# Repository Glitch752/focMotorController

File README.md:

# FOCMotorController

A 12v brushless DC motor controller capable of [field-oriented control](https://en.wikipedia.org/wiki/Vector_control_(motor)) (also known as vector control), which is a control system concept that can improve the efficiency and power output of motors using current-based feedback.

I wanted to learn how field-oriented control systems (and brushless motor controllers in general) work, so I made a PCB from scratch!

</img>

## Design goals
- Allow 30-amp continuous operation
- Run field-oriented control
- Runs off an RP2040 Arduino devboard
- Operate at relatively high efficiency: I don't have a specific goal in mind, but ideally it would experience less than a few watts loss at peak load
- Allow controlling the [REV NEO](https://www.revrobotics.com/rev-21-1650/) series motors from the FRC ecosystem because I have access to many old ones.
- Record accurate quadrature encoder readings for tight closed-loop control
- Build for under $200

## Bill of materials

There are a few main components I needed to choose for this project:
- **MOSFETs:** This is pretty much just a tradeoff between efficiency, size, and price. I landed on the STM [STP55NF06L](https://www.st.com/content/ccc/resource/technical/document/datasheet/49/c5/a8/71/93/60/4f/86/CD00002690.pdf/files/CD00002690.pdf/jcr:content/translations/en.CD00002690.pdf) power MOSFET,
which has a very low static resistance when on with a gate voltage of >10V. At only 3.3V, the resistance is quite high, meaning we need a gate driver circuit to improve the driver's efficiency.
- **Gate drivers**: I chose the [IR2104](https://www.infineon.com/dgdl/Infineon-IR2104-DS-v01_00-EN.pdf?fileId=5546d462533600a4015355c7c1c31671) half-bridge gate drivers primarily because they're cheap and widely available.
Also, since they're half-bridge, they manage both the voltage and ground MOSFETs for their phase, which simplifies the control logic.
- **Current measurement circuitry**: There are [quite a few methods available for sensing current](https://www.nxp.com/docs/en/application-note/AN14164.pdf) in motor controllers, but the simplest is using a shunt resistor and relying on Ohm's law.
This is what I ended up doing. I use a [INA240 amplifier](https://www.ti.com/lit/ds/symlink/ina240.pdf) reading across a 6mΩ resistor to convert the tiny voltage potential difference to something readable by the microcontroller.
I'm interested to see what the signal-to-noise ratio will look like.
- Other miscellaneous things like logic level shifters because we're using a 3.3v microcontroller and 5v encoders. All components use a relatively large form-factor where possible to make hand-soldering simpler (altough there are a few tiny SMT components).

Here are all the components required and their price as of July 2025 from JLCPCB.
Of course, many of these can be sourced cheaper elsewhere and soldered manually.

|Name     |Purpose|Quantity|JLC part number|Total Price|
|---------|-------|--------|---------------|-----------|
|STP55NF06L|The main MOSFET we use|6|[C77582](https://jlcpcb.com/partdetail/STMicroelectronics-STP55NF06L/C77582)|$5.91|
|IR2104STRPBF|The main gate drivers|3|[C2960](https://jlcpcb.com/partdetail/InfineonTechnologies-IR2104STRPBF/C2960)|$1.15|
|Arduino Nano RP2040 Connect|The microcontroller used|1|n/a|$19.10 (on Amazon)|
|SN74LVC2T45DCTR|Level shifters for quadrature encoder input|2|[C22672](https://jlcpcb.com/partdetail/TexasInstruments-SN74LVC2T45DCTR/C22672)|$0.44|
|INA240A1D|The amplifier used for current sensing|3|[C2060769](https://jlcpcb.com/partdetail/TexasInstruments-INA240A1D/C2060769)|$4.32|
|PA2512FKF7W0R006E|The low-resistance 6mΩ shunt resistor|3|[C728340](https://jlcpcb.com/partdetail/YAGEO-PA2512FKF7W0R006E/C728340)|$0.30|
|A16-1000|A resettable fuse for the power input|1|[C135398](https://jlcpcb.com/partdetail/Shenzhen_JDTFuse-A161000/C135398)|$0.09|
|KM477M035F16RR0VH2FP0|470uF capacitor for input smoothing|1|[C47888](https://jlcpcb.com/partdetail/48894-KM477M035F16RR0VH2FP0/C47888)|$0.05|
|KM477M035F16RR0VH2FP0|0.1uF capacitor for input smoothing|1|[C47888](https://jlcpcb.com/partdetail/48894-KM477M035F16RR0VH2FP0/C47888)|$0.05|
|50YXF1MEFC5X11|1uF capacitor for decoupling gate drivers|3|[C2927584](https://jlcpcb.com/partdetail/Rubycon-50YXF1MEFC5X11/C2927584)|$0.13|
|CC1H104MC1FD3F6C10SA|100nF capacitor for bootstrapping|3|[C5375966](https://jlcpcb.com/partdetail/Dersonic-CC1H104MC1FD3F6C10SA/C5375966)|$0.07|
|S6B-PH-K-S(LF)(SN)|6-pin JST connector for encoder|1|[C157920](https://jlcpcb.com/partdetail/JST-S6B_PH_K_S_LF_SN/C157920)|$0.07|
|XL-3216UGC-FB|Green status LEDs|3|[C3646937](https://jlcpcb.com/partdetail/XINGLIGHT-XL_3216UGCFB/C3646937)|$0.04|
|XL-3216SURC-FB|Red power LED|1|[C3646938](https://jlcpcb.com/partdetail/XINGLIGHT-XL_3216SURCFB/C3646938)|$0.01|
|B0530W|500mA diode for bootstrap power|3|[B0530W](https://jlcpcb.com/partdetail/2459-B0530W/C2102)|$0.10|
|MBR1045G|10A Schottky Diode for power source|1|[C79734](https://jlcpcb.com/partdetail/onsemi-MBR1045G/C79734)|$0.86|
|SMAJ15A|TVS diode for voltage spike protection|1|[C113958](https://jlcpcb.com/partdetail/115197-SMAJ15A/C113958)|$0.04|
|WJ128V-5.0-3P|Screw terminal block for phase output|1|[C8270](https://jlcpcb.com/partdetail/Ningbo_KangnexElec-WJ128V_5_03P/C8270)|$0.16|
|WJ128V-5.0-2P|Screw terminal block for voltage input|1|[C8269](https://jlcpcb.com/partdetail/Ningbo_KangnexElec-WJ128V_5_02P/C8269)|$0.11|
|1206W4J0332T5E|3.3kohm resistor, misc|1|[C26041](https://jlcpcb.com/partdetail/26784-1206W4J0332T5E/C26041)|$0.01|
|1206W4F2001T5E|2kohm resistor, misc|1|[C17944](https://jlcpcb.com/partdetail/18632-1206W4F2001T5E/C17944)|$0.01|
|1206W4J0621T5E|620ohm resistor, misc|1|[C25391](https://jlcpcb.com/partdetail/26134-1206W4J0621T5E/C25391)|$0.01|
|FRC1206J101 TS|100ohm resistor, misc|3|[C2907422](https://jlcpcb.com/partdetail/FOJAN-FRC1206J101TS/C2907422)|$0.01|
|1206W4F4702T5E|47kohm pulldown resistors|4|[C25833](https://jlcpcb.com/partdetail/26576-1206W4F4702T5E/C25833)|$0.02|
|FRC1206F19R6TS|19.6ohm gate resistors|6|[C2933621](https://jlcpcb.com/partdetail/FOJAN-FRC1206F19R6TS/C2933621)|$0.02|

Total part cost for 1 board:
- $8.02 without microcontroller or MOSFETs
- $13.93 without microcontroller
- $33.03 with microcontroller   

Note that, if you're doing assembly through something like JLCPCB, you'll need to make 5. If you don't need 5 boards, you can avoid assembly for the MOSFETs and order them yourself. They're one of the easiest components to solder on the board.

## FOC writeup
Here, I'll document my current knowledge of field oriented control for my own reference and to see what I need to look further into. Please note all this information may not be correct since BLDC control is still a new subject to me.

Field oriented control is a mechanism to control brushless DC motors that guarantees torque will always be applied directly perpendicular to the motor. It increases the efficiency, maximum speed, and power output of controlled motors. However, it's also relatively expensive to calculate and suffers from MOSFET switching losses because we must use PWM control to generate an effective sine wave.

### Definitions and acronyms
- **Motor**: A device that converts electrical energy into mechanical energy. Motors typically use moving permanent magnets and fixed electromagnets to generate a magnetic field that causes the rotor to spin.
  - **Winding**: A coil of wire that generates a magnetic field when current flows through it.
  - **Inductor**: Another name for a winding, typically used in the context of inductors that store energy in a magnetic field.
  - **Phase**: A set of windings in a motor that is independently controlled. Brushless motors typically have three phases, which are often referred to as A, B, and C or U, V, and W.
  - **Rotor**: The *rot*ating part of the motor containing permanent magnets. This is the part that spins.
    - **Poles**: The number of permanent magnets attached to the rotor. This isn't necessarily a multiple of the number of phases, but should be a multiple of 2 (since two identical magnet poles can't be beside each other).
  - **Stator**: The *stat*ionary part of the motor containing the windings. This is the part that generates the magnetic field. In a 3-phase motor, the stator has 3 sets of windings, each 120 electric degrees apart.
    - **Slots**: The number of coils on the stator. Motors will have a number of slots that is a multiple of the number of phases.
  - **BLDC**: Brushless DC. Brushed motors have physical contacts that dictate when phases are activated, while brushless motors rely on electrical signals to control the phases. Brushless motors can be faster, more reliable, and more efficient, but this comes at the cost of complexity.[<sup>1</sup>](#footnote-1)
  - **PMSM**: Permanent Magnet Synchronous Motors. The uses of this term are somewhat murky and confused with BLDC, so I will refrain from using it to avoid confusion.[<sup>2</sup>](#footnote-2)
  - **Mechanical angle**: The physical angle of the rotor in the motor; 1 revolution of the rotor is 360 degrees. The mechanical angle is used for position and speed feedback.
  - **Electrical angle**: The electrical angle describes the position of the rotor relative to the stator's magnetic field. It cycles faster than the mechanical angle by a factor equal to the number of pole pairs. The electrical angle is used for control calculations (e.g. it's the angle used in park and clarke transformations; see below).
- **FOC**: Field-oriented control, a method of controlling brushless motors that uses current-based feedback to apply torque directly perpendicular to the rotor.
- **Inverter**: Components that convert DC power to AC power. In our case, the circuitry that converts the motor controller's input voltage to phase voltages.
  - **MOSFET**: Metal-Oxide-Semiconductor Field-Effect Transistor; a particular type of transistor that can effectively act as a switch when appropriate signals are applied. 6 MOSFETs are used for BLDC motor control: one for ground and one for voltage of each phase.
  - **Gate driver / FET driver**: A circuit that controls MOSFETs, providing the necessary voltage while decoupling the microcontroller from the relatively high current draw of switching MOSFETs.
  - **Half bridge**: A circuit that controls two MOSFETs to switch a phase between voltage and ground. Half bridges are used for each phase in BLDC motor control.
- **Encoder**: A device that measures the position of the rotor relative to the stator. Accurate position measurement is crucial for FOC so we know where to apply torque.
  - **Hall effect sensor**: A type of sensor that detects magnetic fields.
  - **Quadrature encoder**: A type of encoder that uses two signals to determine the position of the rotor. It can detect both position and direction of rotation. Quadrature encoders can use hall sensors, optical sensors, or other methods.
    - **A/B channels**: Quadrature encoders have two primary outputs, A and B, which are 90 degrees out of phase. This communicates both velocity and direction of rotation.
    - **C channel / index**: Some quadrature encoders (including those we rely on) have a third channel, C, which indicates a specific position of the rotor. This is used for homing the rotor to find its initial position.
- **PWM**: Pulse-width modulation. A method of controlling the amount of power delivered by quicking switching something on and off.
  - **Duty cycle**: The percentage of time that a signal is on compared to the total time. For example, a 25% duty cycle means the signal is on for 25% of the time and off for 75% of the time.
  - **SVM**: Space vector modulation. An algorithm for effectively creating AC waveforms through PWM signals. SVM is commonly used for BLDC motor control because it reduces noise and vibration compared to more naive approaches.
- **Driving frequency**: Generally, the frequency of PWM pulses sent to the half bridge drivers. A higher driving frequency creates a smoother output signal but requires faster and more expensive hardware. Generally in the range of 20 to 80 kHz.
- **Control frequency**: The frequency of the control system driving the output voltages. Control systems generally operate around 1 to 5 kHz.
- **Inrunner/outrunner**: Two types of brushless motors that differ in how the stator and rotor are arranged.
  - **Inrunner**: The rotor is inside the stator, which typically contains large windings pointing inward. Inrunner motors generally have a higher maximum speed and efficiency.
  - **Outrunner**: The rotor is outside the stator, which typically contains smaller windings pointing outward. In some cases, this means the rotor is the outer body of the motor. In outrunner motors, the rotor is sometimes also called a can. Outrunner motors generally have a higher torque output.
- **Flux**: Shorthand for magnetic flux linkage. Magnetic flux linkage can be thought of as the "magnetic field strength" in the motor. For PMSM control, our reference flux is 0 (but we still need to control it to keep it there).
- There are many coordinate systems used for BLDC control; see [figure 1](#figure-1-a-diagram-of-coordinate-systems-used-in-foc). Here are the most important ones and their common names:
  - **Stator X axis / alpha**: The "horizontal" (on a side profile) axis of the motor stator.
  - **Stator Y axis / beta**: The "vertical" (on a side profile) axis of the motor stator.
  - **Winding U, V, and W axes**: The axes pointing outwards for the three phases of the motor, 120 degrees offset from each other. Axis U is typically aligned with the stator X axis.
  - **Rotor direct axis / d**: The axis of the rotor that is parallel to the rotor's magnetic field that generates flux.
  - **Rotor quadrature axis / q**: The axis of the rotor that is perpendicular to the rotor's magnetic field that generates torque.
- **Electromotive force / back EMF**: The voltage generated by the motor itself while spinning.[<sup>3</sup>](#footnote-3)
- Transformations are used in motor control to make manipulating the signals simpler.
  - **Clarke transformation**: Also known as the alpha-beta transformation; converts the three-phase stator currents u, v, and w into stator axes alpha and beta.
  - **Park transformation**: Also known as the direct-quadrature-zero transformation; converts stator-aligned components into rotor axes q and d with respect to the motor's rotating magnetic field.
- **Proportional-integral (PI) controller**: A feedback-based control mechanism to regulate processes that require dynamic adjustment or can't be precisely modelled mathematically. PI controllers are used to regulate rotor axis (q and d) currents by controlling the maximum PWM duty cycle for each phase.[<sup>4</sup>](#footnote-4)

### FOC process

The broad overview of FOC control is as follows:
1. Gather the measured position of the rotor using the encoder.
2. Transform phases into the rotor coordinate system.
3. Calculate the required current in the rotor quadrature axis (q) to generate the desired torque.
4. Calculate the required current in the rotor direct axis (d) to generate the desired magnetic field.
5. Transform the rotor coordinate system back to the phases' coordinate systems.
6. Calculate the required voltage to apply to each phase to generate the desired current.
7. Apply the calculated voltage to each phase using PWM.
8. Repeat at a high frequency.

From [this great presentation](https://www.ti.com/lit/ml/slyp711/slyp711.pdf).  

There are a few important things to note:
- We can't track the encoder position fast enough to respond accurately to the rotor position at high speeds,
  so we must perform latency compensation of some sort.
- The current in the rotor direct axis (d) is typically set to zero, meaning we only control the rotor quadrature axis (q).
  This is because the d-axis current doesn't generate torque, so we don't care about it for most applications.
- This doesn't account for current limiting, which is a whole separate topic that I honestly
  don't understand very well. Currently, I naively clamp the applied current to a maximum value.

### Footnotes

<h4 id="footnote-1"><sup>1</sup> "Brushless DC"</h4>
Confusingly, "brushless DC motor control" is often used to refer to brushless motors that are controlled with DC voltage through a motor controller, even though the motor itself is an AC motor. This is because the motor controller generates a sine wave using PWM signals, which is then applied to the motor phases.

<h4 id="footnote-2"><sup>2</sup> "Permanent Magnet Synchronous Motors. The uses of this term are somewhat murky and confused with BLDC [...]"</h4>
Technically, brushless motors can also be switched reluctance motors or induction motors (also known as asynchronous motors). However, the majority of brushless DC motors are PMSM. Synchronous motors are a subset of brushless motors whose speed is independent of the load.

<h4 id="footnote-3"><sup>3</sup> "Back EMF is the voltage generated by the motor itself while spinning"</h4>
When brushless motors spin, the rotor generates current in the stator that opposes the applied voltage. Back EMF is linearly proportional to the rotational speed of the motor, so it's one of the forces that limits brushless motors' maximum speed.  
Back EMF is sometimes used to determine the position and speed of brushless motors in sensorless control, but almost never for FOC because it's not precise enough. It can also be used to our advantage for "braking", which entails shorting the phases together to make the motor resist rotation.  
  
<h4 id="footnote-4"><sup>4</sup> "PI controllers are a feedback-based control mechanism [...]"</h4>
PI controllers take the error between the current and desired state as an input and adjust the output based on the error. They have two components (hence the name): a proportional component that linearly adjusts the output based on the error, and an integral component that accumulates error over time. The two components are added to get the final output.  
PI controllers are a subset of the more general PID controllers, which also include a derivative component that predicts future error based on the rate of change of the error. In a PI controller, the components serve different purposes; the proportional component provides immediate response to error, while the integral component helps eliminate steady-state error by adjusting the output based on accumulated error over time.  

### Figures
#### Figure 1: A diagram of coordinate systems used in FOC

## Software
Currently, there's a testing piece of software written in Python to run on a local system and simulate the motor controller.
Obviously, Python won't be fast enough for high-speed closed-loop control on the motor controller,
so I'll move to C++ once I have the ability to test more easily.

## Hackatime
Project name: `focMotorController`

Note that I initially had some issues with kicad-wakatime, so it didn't track ~8 hours of work :(

## Future investigation (once I actually have a PCB lol)
- Does it actually work?
- Do we need a heatsink? We should be dissipating an average of ~0.32W per MOSFET at peak load, and 2 watts spread over 6 devices is a very minimal amount of heat. Maybe if we drive it harder, but the rest of the circuit would probably break before the MOSFETs...
- There's an interesting new-ish algorithm seen primarily in acadamia called [Deadbeat Direct Torque and Flux Control](https://www.mdpi.com/1996-1073/15/9/3009); how difficult would it be to implement this?
- Understand and determine the advantages of [discontinuous PWM](https://imperix.com/doc/implementation/discontinuous-pwm) signaling

### Future investigation for the PCB
- Should we have separate enable lines per half bridge?
- Is there a more efficient and accurate, yet inexpensive, way to measure current?
- How can I minimize signal noise in a board carrying high current?
- How can I improve the gate driver circuitry to minimize switching losses?
- Should we instead use full half bridge chips instead of drivers and MOSFETs?

## Resources
- [Current Sensing Techniques in Motor Control Applications - NXP](https://www.nxp.com/docs/en/application-note/AN14164.pdf)
- [Bootstrap Circuitry Selection for Half Bridge Configurations - Texas Instruments](https://www.ti.com/lit/an/slua887a/slua887a.pdf)
- [Bypass Capacitor, Its Functions and Applications - Elprocus](https://www.elprocus.com/bypass-capacitor-its-functions-and-applications/)
- [How to Make Advanced BLDC Motor Controllers - Altium](https://resources.altium.com/p/build-advanced-brushless-motor-controller)
- [Field-Oriented Control (FOC) for BLDC Motors: A Beginner’s Guide - Mechtex](https://mechtex.com/blog/field-oriented-control-foc-for-bldc-motors-a-beginners-guide)
- [Discontinuous PWM (DPWM) - Imperix](https://imperix.com/doc/implementation/discontinuous-pwm)
- [Proportional–integral–derivative controller](https://en.wikipedia.org/wiki/Proportional%E2%80%93integral%E2%80%93derivative_controller)
- [Space vector modulation - Wikipedia](https://en.wikipedia.org/wiki/Space_vector_modulation)
- [Space Vector PWM Intro - Switchcraft](https://www.switchcraft.org/learning/2017/3/15/space-vector-pwm-intro) (has great animations)
- [Protect Your BLDC Motor Drive with Cycle-by-cycle Current Limit Control - Texas Instruments](https://www.ti.com/lit/ta/ssztbp2/ssztbp2.pdf)
- [PMSM Control with DSCs and MCUs - Microchip](https://www.microchip.com/en-us/solutions/technologies/motor-control-and-drive/motor-types/permanent-magnet-synchronous-motors)
- [Vector control (motor) - Wikipedia](https://en.wikipedia.org/wiki/Vector_control_(motor))
- [Demystifying BLDC motor commutation - Texas Instruments](https://www.ti.com/lit/ml/slyp711/slyp711.pdf)
- [Alpha–beta transformation - Wikipedia](https://en.wikipedia.org/wiki/Alpha%E2%80%93beta_transformation)
- [Direct-quadrature-zero transformation - Wikipedia](https://en.wikipedia.org/wiki/Direct-quadrature-zero_transformation)
- [Field Oriented Control (FOC) - A Deep Dive - Performance Motion Devices](https://www.pmdcorp.com/resources/type/articles/get/field-oriented-control-foc-a-deep-dive-article)
- [fasaxc/pico-bldc - Github](https://github.com/fasaxc/pico-bldc/tree/main)

### Datasheets
- [INA240 Bidirectional, Ultra-Precise Current Sense Amplifier](https://www.ti.com/lit/ds/symlink/ina240.pdf)
- [Datasheet IR2104(S) & (PbF)](https://www.infineon.com/dgdl/Infineon-IR2104-DS-v01_00-EN.pdf?fileId=5546d462533600a4015355c7c1c31671)
- [Datasheet STP55NF06L N-channel Power MOSFET](https://www.st.com/content/ccc/resource/technical/document/datasheet/49/c5/a8/71/93/60/4f/86/CD00002690.pdf/files/CD00002690.pdf/jcr:content/translations/en.CD00002690.pdf)

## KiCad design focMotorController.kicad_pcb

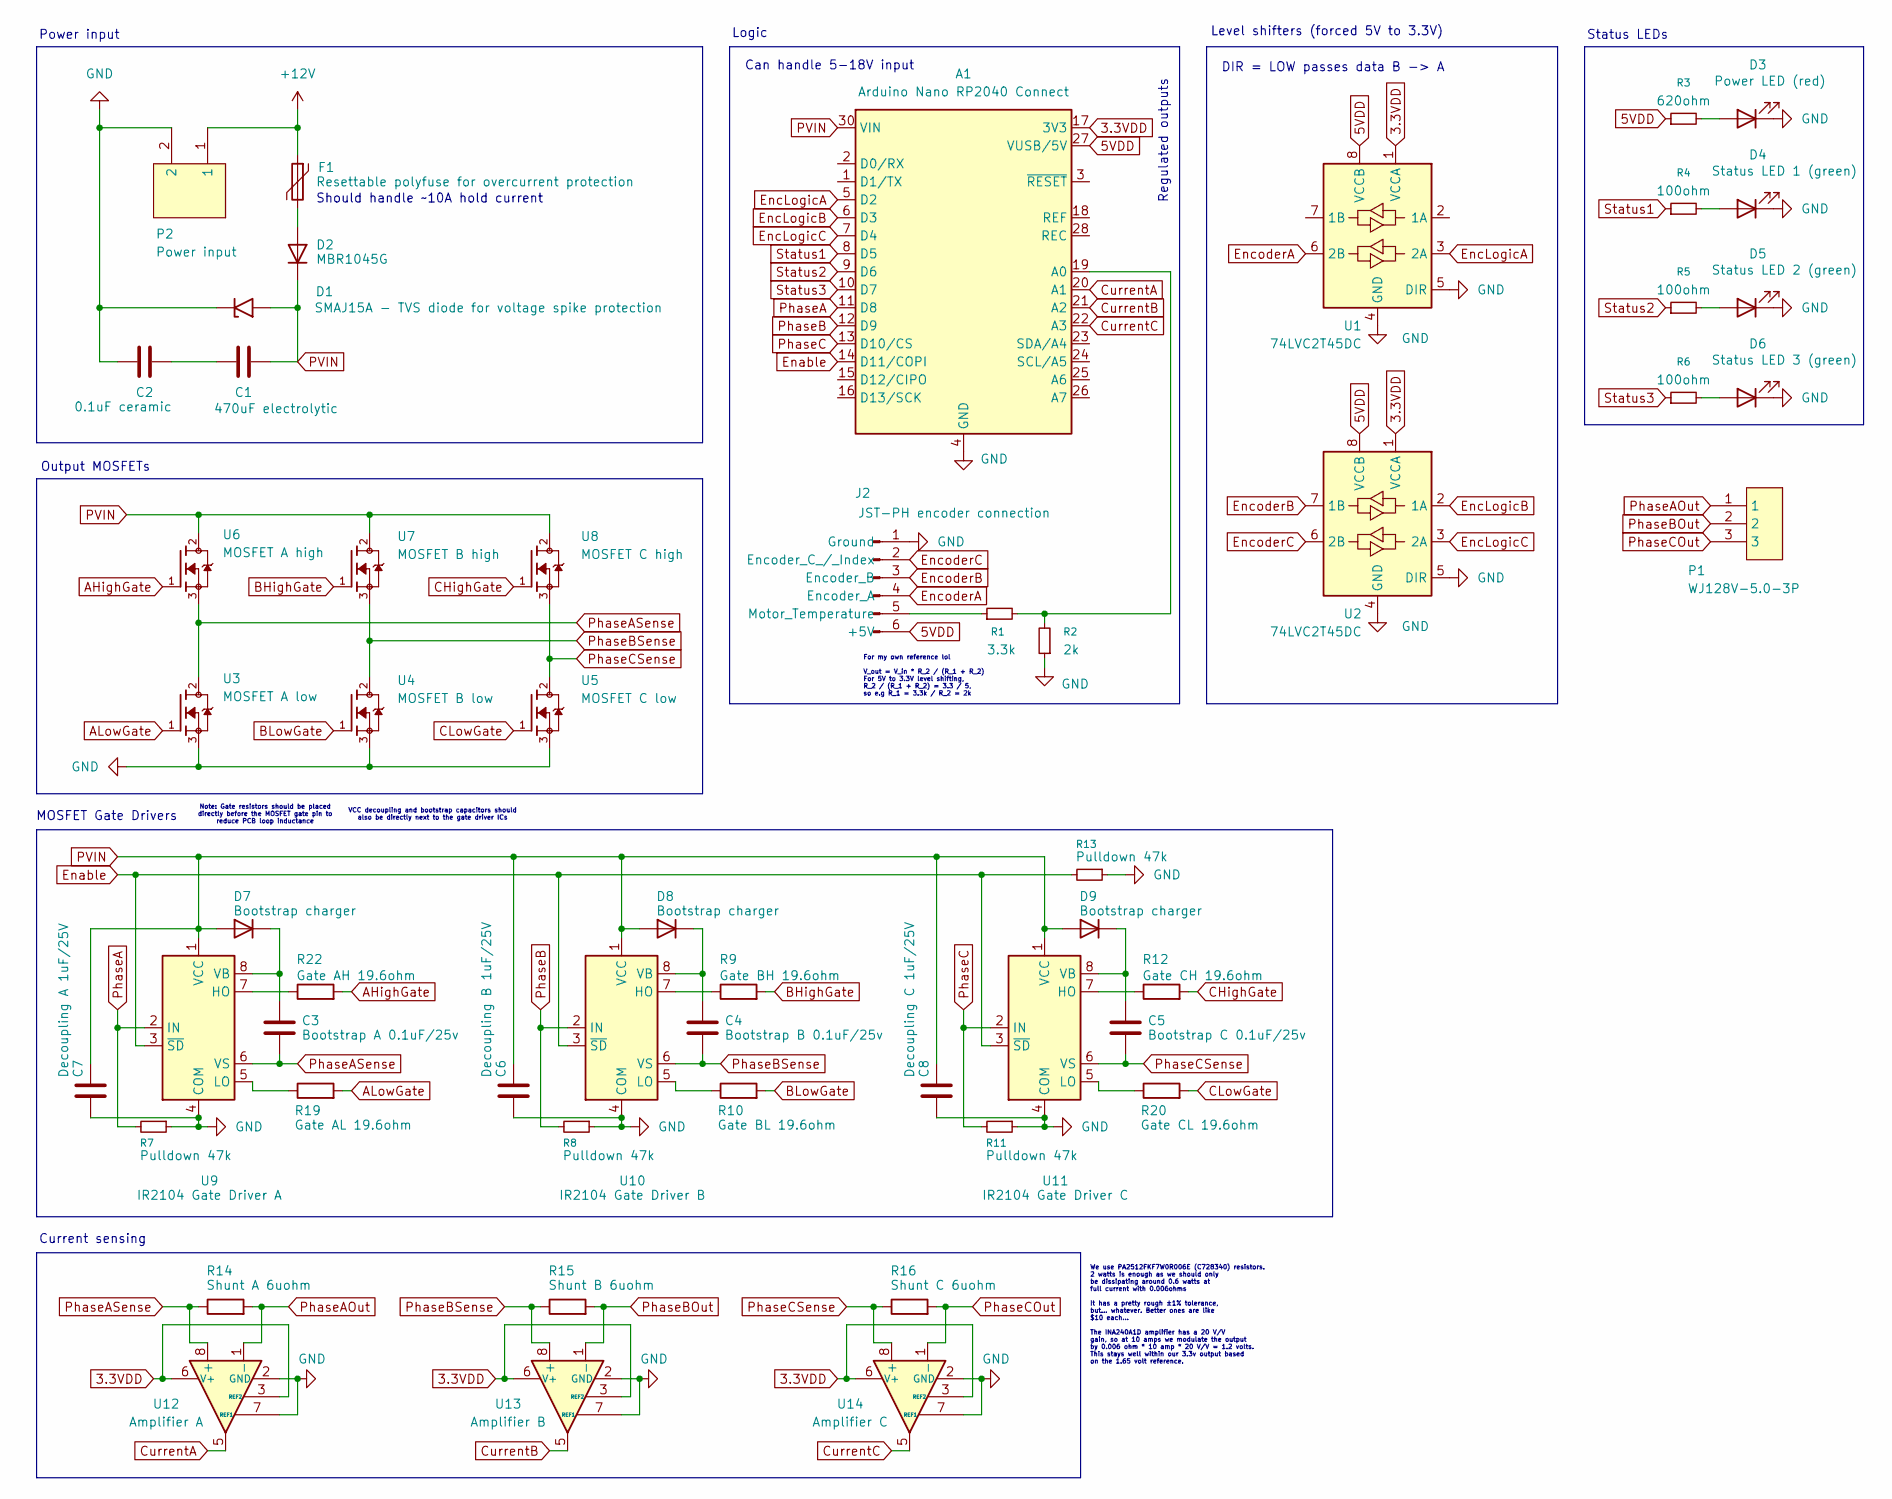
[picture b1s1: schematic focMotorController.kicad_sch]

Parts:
A1: Arduino Nano RP2040 Connect; Arduino_Nano
C1: 470uF electrolytic; CP_Radial_D8.0mm_P3.50mm
C2: 0.1uF ceramic; C_Disc_D5.0mm_W2.5mm_P5.00mm
C3: Bootstrap A 0.1uF/25v; C_Disc_D5.0mm_W2.5mm_P5.00mm
C4: Bootstrap B 0.1uF/25v; C_Disc_D5.0mm_W2.5mm_P5.00mm
C5: Bootstrap C 0.1uF/25v; C_Disc_D5.0mm_W2.5mm_P5.00mm
C6: Decoupling B 1uF/25V; CP_Radial_D5.0mm_P2.00mm
C7: Decoupling A 1uF/25V; CP_Radial_D5.0mm_P2.00mm
C8: Decoupling C 1uF/25V; CP_Radial_D5.0mm_P2.00mm
D1: SMAJ15A - TVS diode for voltage spike protection; D_SMA
D2: MBR1045G; TO-220-2_Vertical
D3: Power LED (red); LED_1206_3216Metric
D4: Status LED 1 (green); LED_1206_3216Metric
D5: Status LED 2 (green); LED_1206_3216Metric
D6: Status LED 3 (green); LED_1206_3216Metric
D7, D8, D9: Bootstrap charger; D_SOD-123
F1: Resettable polyfuse for overcurrent protection; A16-1000
J2: JST-PH encoder connection; JST_PH_S6B-PH-K_1x06_P2.00mm_Horizontal
P1: WJ128V-5.0-3P; LCSC Part C8270
P2: Power input; WJ128V-5.0-2P; LCSC Part C8269
R1: 3.3k; R_1206_3216Metric
R2: 2k; R_1206_3216Metric
R3: 620ohm; R_1206_3216Metric
R4, R5, R6: 100ohm; R_1206_3216Metric
R7, R8, R11, R13: Pulldown 47k; R_1206_3216Metric
R9: Gate BH 19.6ohm; R_1206_3216Metric
R10: Gate BL 19.6ohm; R_1206_3216Metric
R12: Gate CH 19.6ohm; R_1206_3216Metric
R14: Shunt A 6uohm; R_2512_6332Metric
R15: Shunt B 6uohm; R_2512_6332Metric
R16: Shunt C 6uohm; R_2512_6332Metric
R19: Gate AL 19.6ohm; R_1206_3216Metric
R20: Gate CL 19.6ohm; R_1206_3216Metric
R22: Gate AH 19.6ohm; R_1206_3216Metric
U1, U2: 74LVC2T45DC; VSSOP-8_2.3x2mm_P0.5mm
U3: MOSFET A low; STP55NF06L
U4: MOSFET B low; STP55NF06L
U5: MOSFET C low; STP55NF06L
U6: MOSFET A high; STP55NF06L
U7: MOSFET B high; STP55NF06L
U8: MOSFET C high; STP55NF06L
U9: IR2104 Gate Driver A; IR2104SPBF
U10: IR2104 Gate Driver B; IR2104SPBF
U11: IR2104 Gate Driver C; IR2104SPBF
U12: Amplifier A; SOIC-8_3.9x4.9mm_P1.27mm
U13: Amplifier B; SOIC-8_3.9x4.9mm_P1.27mm
U14: Amplifier C; SOIC-8_3.9x4.9mm_P1.27mm

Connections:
3.3VDD: A1.17 (3V3), U1.1 (VCCA), U2.1 (VCCA), U12.3 (REF2), U12.6 (V+), U13.3 (REF2), U13.6 (V+), U14.3 (REF2), U14.6 (V+)
5VDD: A1.27 (VUSB/5V), J2.6 (+5V), R3.1, U1.8 (VCCB), U2.8 (VCCB)
+12V: F1.1, P2.1
AHighGate: R22.2, U6.1
ALowGate: R19.2, U3.1
BHighGate: R9.2, U7.1
BLowGate: R10.2, U4.1
CHighGate: R12.2, U8.1
CLowGate: R20.2, U5.1
CurrentA: A1.20 (A1), U12.5
CurrentB: A1.21 (A2), U13.5
CurrentC: A1.22 (A3), U14.5
Enable: A1.14 (D11/COPI), R13.2, U9.3 (~SD), U10.3 (~SD), U11.3 (~SD)
EncLogicA: A1.5 (D2), U1.3 (2A)
EncLogicB: A1.6 (D3), U2.2 (1A)
EncLogicC: A1.7 (D4), U2.3 (2A)
EncoderA: J2.4 (Encoder_A), U1.6 (2B)
EncoderB: J2.3 (Encoder_B), U2.7 (1B)
EncoderC: J2.2 (Encoder_C_/_Index), U2.6 (2B)
GND: A1.4 (GND), A1.29 (GND), C2.1, C6.2, C7.2, C8.2, D1.1 (A1), D3.1 (K), D4.1 (K), D5.1 (K), D6.1 (K), J2.1 (Ground), P2.2, R2.1, R7.1, R8.1, R11.1, R13.1, U1.4 (GND), U1.5 (DIR), U2.4 (GND), U2.5 (DIR), U3.3, U4.3, U5.3, U9.4 (COM), U10.4 (COM), U11.4 (COM), U12.2 (GND), U12.4 (GND), U12.7 (REF1), U13.2 (GND), U13.4 (GND), U13.7 (REF1), U14.2 (GND), U14.4 (GND), U14.7 (REF1)
unnamed: A1.19 (A0), R1.2, R2.2
unnamed: C1.1, C2.2
unnamed: D2.2 (A), F1.2
unnamed: D3.2 (A), R3.2
unnamed: D4.2 (A), R4.2
unnamed: D5.2 (A), R5.2
unnamed: D6.2 (A), R6.2
unnamed: C3.1, D7.1 (K), U9.8 (VB)
unnamed: C4.1, D8.1 (K), U10.8 (VB)
unnamed: C5.1, D9.1 (K), U11.8 (VB)
unnamed: J2.5 (Motor_Temperature), R1.1
unnamed: R22.1, U9.7 (HO)
unnamed: R19.1, U9.5 (LO)
unnamed: R9.1, U10.7 (HO)
unnamed: R10.1, U10.5 (LO)
unnamed: R12.1, U11.7 (HO)
unnamed: R20.1, U11.5 (LO)
PVIN: A1.30 (VIN), C1.2, C6.1, C7.1, C8.1, D1.2 (A2), D2.1 (K), D7.2 (A), D8.2 (A), D9.2 (A), U6.2, U7.2, U8.2, U9.1 (VCC), U10.1 (VCC), U11.1 (VCC)
PhaseA: A1.11 (D8), R7.2, U9.2 (IN)
PhaseAOut: P1.1, R14.2, U12.1 (-)
PhaseASense: C3.2, R14.1, U3.2, U6.3, U9.6 (VS), U12.8 (+)
PhaseB: A1.12 (D9), R8.2, U10.2 (IN)
PhaseBOut: P1.2, R15.2, U13.1 (-)
PhaseBSense: C4.2, R15.1, U4.2, U7.3, U10.6 (VS), U13.8 (+)
PhaseC: A1.13 (D10/CS), R11.2, U11.2 (IN)
PhaseCOut: P1.3, R16.2, U14.1 (-)
PhaseCSense: C5.2, R16.1, U5.2, U8.3, U11.6 (VS), U14.8 (+)
Status1: A1.8 (D5), R4.1
Status2: A1.9 (D6), R5.1
Status3: A1.10 (D7), R6.1

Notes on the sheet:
Can handle 5-18V input
VCC decoupling and bootstrap capacitors should also be directly next to the gate driver ICs
Logic
MOSFET Gate Drivers
Output MOSFETs
We use PA2512FKF7W0R006E (C728340) resistors. 2 watts is enough as we should only be dissipating around 0.6 watts at full current with 0.006ohms It has a pretty rough ±1% tolerance, but... whatever. Better ones are like $10 each... The INA240A1D amplifier has a 20 V/V gain, so at 10 amps we modulat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
For my own reference lol V_out = V_in * R_2 / (R_1 + R_2) For 5V to 3.3V level shifting, R_2 / (R_1 + R_2) = 3.3 / 5, so e.g R_1 = 3.3k / R_2 = 2k
Status LEDs
Regulated outputs
DIR = LOW passes data B -> A
Level shifters (forced 5V to 3.3V)
Power input
Should handle ~10A hold current
Current sensing
Note: Gate resistors should be placed directly before the MOSFET gate pin to reduce PCB loop inductance

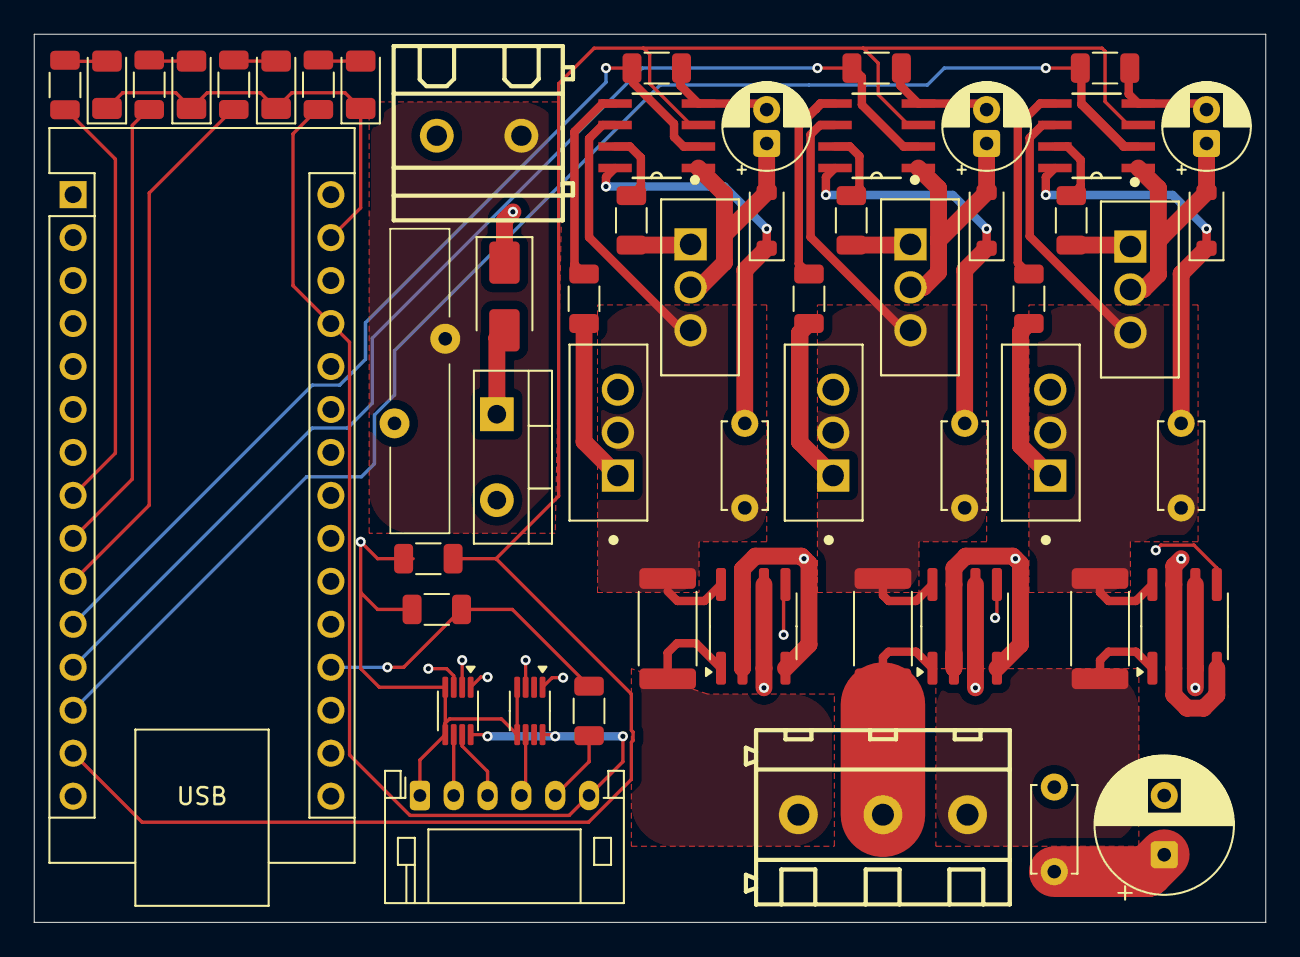
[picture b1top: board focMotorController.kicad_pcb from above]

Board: 4 copper layers, 72.8 x 52.5 mm, 55 parts (0 on the bottom side), 50 nets.

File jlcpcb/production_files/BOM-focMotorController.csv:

Comment,Designator,Footprint,LCSC,Quantity
SMAJ15A - TVS diode for voltage spike protection,D1,D_SMA,C113958,1
Resettable polyfuse for overcurrent protection,F1,A16-1000,C135398,1
JST-PH encoder connection,J2,JST_PH_S6B-PH-K_1x06_P2.00mm_Horizontal,C157920,1
2k,R2,R_1206_3216Metric,C17944,1
Amplifier A,"U12,U13,U14",SOIC-8_3.9x4.9mm_P1.27mm,C2060769,3
Bootstrap charger,"D7,D8,D9",D_SOD-123,C2102,3
74LVC2T45DC,"U1,U2",VSSOP-8_2.3x2mm_P0.5mm,C22672,2
620ohm,R3,R_1206_3216Metric,C25391,1
Pulldown 47k,"R11,R13,R7,R8",R_1206_3216Metric,C25833,4
3.3k,R1,R_1206_3216Metric,C26041,1
100ohm,"R4,R5,R6",R_1206_3216Metric,C2907422,3
Decoupling B 1uF/25V,"C6,C7,C8",CP_Radial_D5.0mm_P2.00mm,C2927584,3
Gate BL 19.6ohm,"R10,R12,R19,R20,R22,R9",R_1206_3216Metric,C2933621,6
IR2104 Gate Driver B,"U10,U11,U9",IR2104SPBF,C2960,3
Status LED 1 (green),"D4,D5,D6",LED_1206_3216Metric,C3646937,3
Power LED (red),D3,LED_1206_3216Metric,C3646938,1
0.1uF ceramic,C2,C_Disc_D5.0mm_W2.5mm_P5.00mm,C400087,1
470uF electrolytic,C1,CP_Radial_D8.0mm_P3.50mm,C47888,1
Bootstrap A 0.1uF/25v,"C3,C4,C5",C_Disc_D5.0mm_W2.5mm_P5.00mm,C5375966,3
Shunt A 6uohm,"R14,R15,R16",R_2512_6332Metric,C728340,3
MOSFET A low,"U3,U4,U5,U6,U7,U8",STP55NF06L,C77582,6
MBR1045G,D2,TO-220-2_Vertical,C79734,1
Power input,P2,WJ128V-5.0-2P,C8269,1
WJ128V-5.0-3P,P1,WJ128V-5.0-3P,C8270,1

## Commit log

2025-07-09 Initial empty project
2025-07-09 Start creating schematic
    Currently includes:
    - Power input circuitry and filtering
    - Logic: microcontroller and encoder connection
    - Level shifters for encoder
    - Status LEDs
    - Output MOSFETs
2025-07-09 Add current sensing circuitry
2025-07-09 Finish initial routing
2025-07-09 Compact PCB
2025-07-09 Finish initial PCB version
2025-07-09 Slightly better documentation
2025-07-10 Try to model motor with Python program (still a work-in-progress), set up PCB for JLCPCB
2025-07-10 Update schematics with remaining JLCPCB parts, finish BOM, and export manufacturing files
2025-07-11 Slightly improve graphing in controller simulation
2025-07-13 Improve simulation to support individual phases
    I think I have a bunch of stuff mixed up, so I'll need to look further into it. I just threw together a minimal clone of other logic I found, but I am definitely missing some components. I'll need to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
2025-07-13 Create initial FOC writeup
2025-07-14 Clean up transformation and motor simulation code slightly, continue writeup
2025-07-15 Much better motor simulation, better graphing, and more documentation
2025-07-15 Improve simulation UI, implement six-step controller, clean up FOC controller
2025-07-16 Improve FOC control and simulator
2025-07-18 Update readme and add better coordinate systems diagram
2025-07-18 Add copper pours for high current traces and clean up PCB elsewhere
2025-07-18 Fix small issues with copper pours and solder mask
2025-07-18 Fix power plane contacting current sense
